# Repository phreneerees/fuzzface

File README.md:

# fuzzface
NPN fuzzface using 2SD600

Will add description?

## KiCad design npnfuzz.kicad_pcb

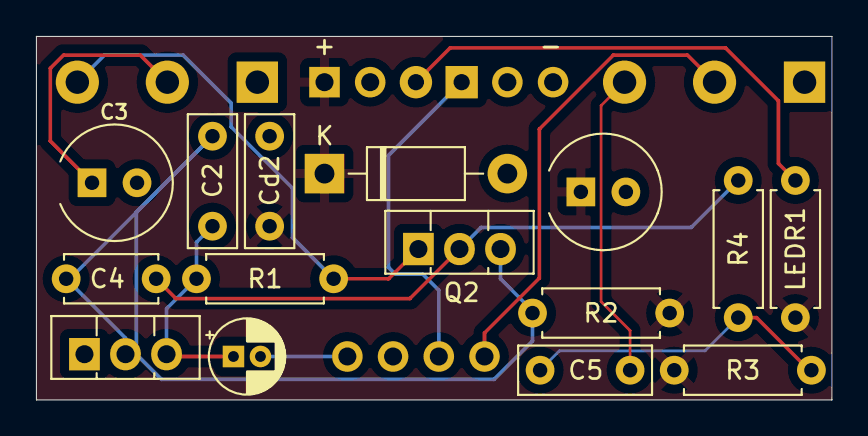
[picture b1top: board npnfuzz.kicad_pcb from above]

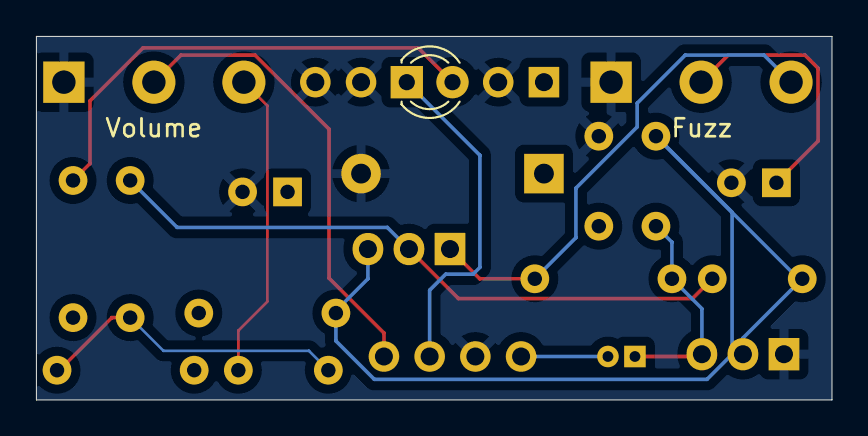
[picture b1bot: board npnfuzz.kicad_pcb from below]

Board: 2 copper layers, 44.2 x 20.2 mm, 24 parts (3 on the bottom side), 13 nets.

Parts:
+: wire_pad_square
-: wire_pad_round
C1: 2u2; CP_Radial_D4.0mm_P1.50mm
C2: 220p; C_classic_RECT
C3: 22u; CP_Radial_NP_D6.3mm_P2.50mm
C4: 47p; C_Disc_D5.0mm_W2.5mm_P5.00mm
C5: 10n; C_classic_RECT
Cd1: 200u; CP_Radial_NP_D6.3mm_P2.50mm
Cd2: 100n; C_classic_RECT
D1: 1N4007; D_DO-41_SOD81_P10.16mm_Horizontal
DLED1: LED; LED_D3.0mm_Clear
Fuzz: 1KB; AlphaPot
GND: power Jack; wire_pad_round
In1: wire_pad_round
L1: wire_pad_round
LEDR1: 2K7; R_classic
Out1: wire_pad_round
Q1, Q2: 2SD600; TO-126-3_Vertical
R1: 100K; R_classic
R2: 33K; R_classic
R3: 330; R_classic
R4: 8K2; R_classic
Volume: 500KA; AlphaPot

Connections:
+9V: +.1, Cd1.1, Cd2.1, D1.1 (K), LEDR1.1, R2.1, R3.1
GND: -.1, C3.2, Cd1.2, Cd2.2, D1.2 (A), Fuzz.1, GND.1, Q1.1 (E), Volume.1
unnamed: C1.2, In1.1
unnamed: C3.1, Fuzz.2
unnamed: C5.1, R3.2, R4.1
unnamed: C5.2, Volume.3
unnamed: DLED1.2 (A), LEDR1.2
unnamed: DLED1.1 (K), L1.1
unnamed: Out1.1, Volume.2
unnamed: C1.1, C2.1, Q1.3 (B), R1.1
unnamed: C2.2, C4.1, Q1.2 (C), Q2.3 (B), R2.2
unnamed: C4.2, Q2.2 (C), R4.2
unnamed: Fuzz.3, Q2.1 (E), R1.2

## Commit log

2024-05-28 Added files
    Good
2024-05-28 Update README.md
    :)
